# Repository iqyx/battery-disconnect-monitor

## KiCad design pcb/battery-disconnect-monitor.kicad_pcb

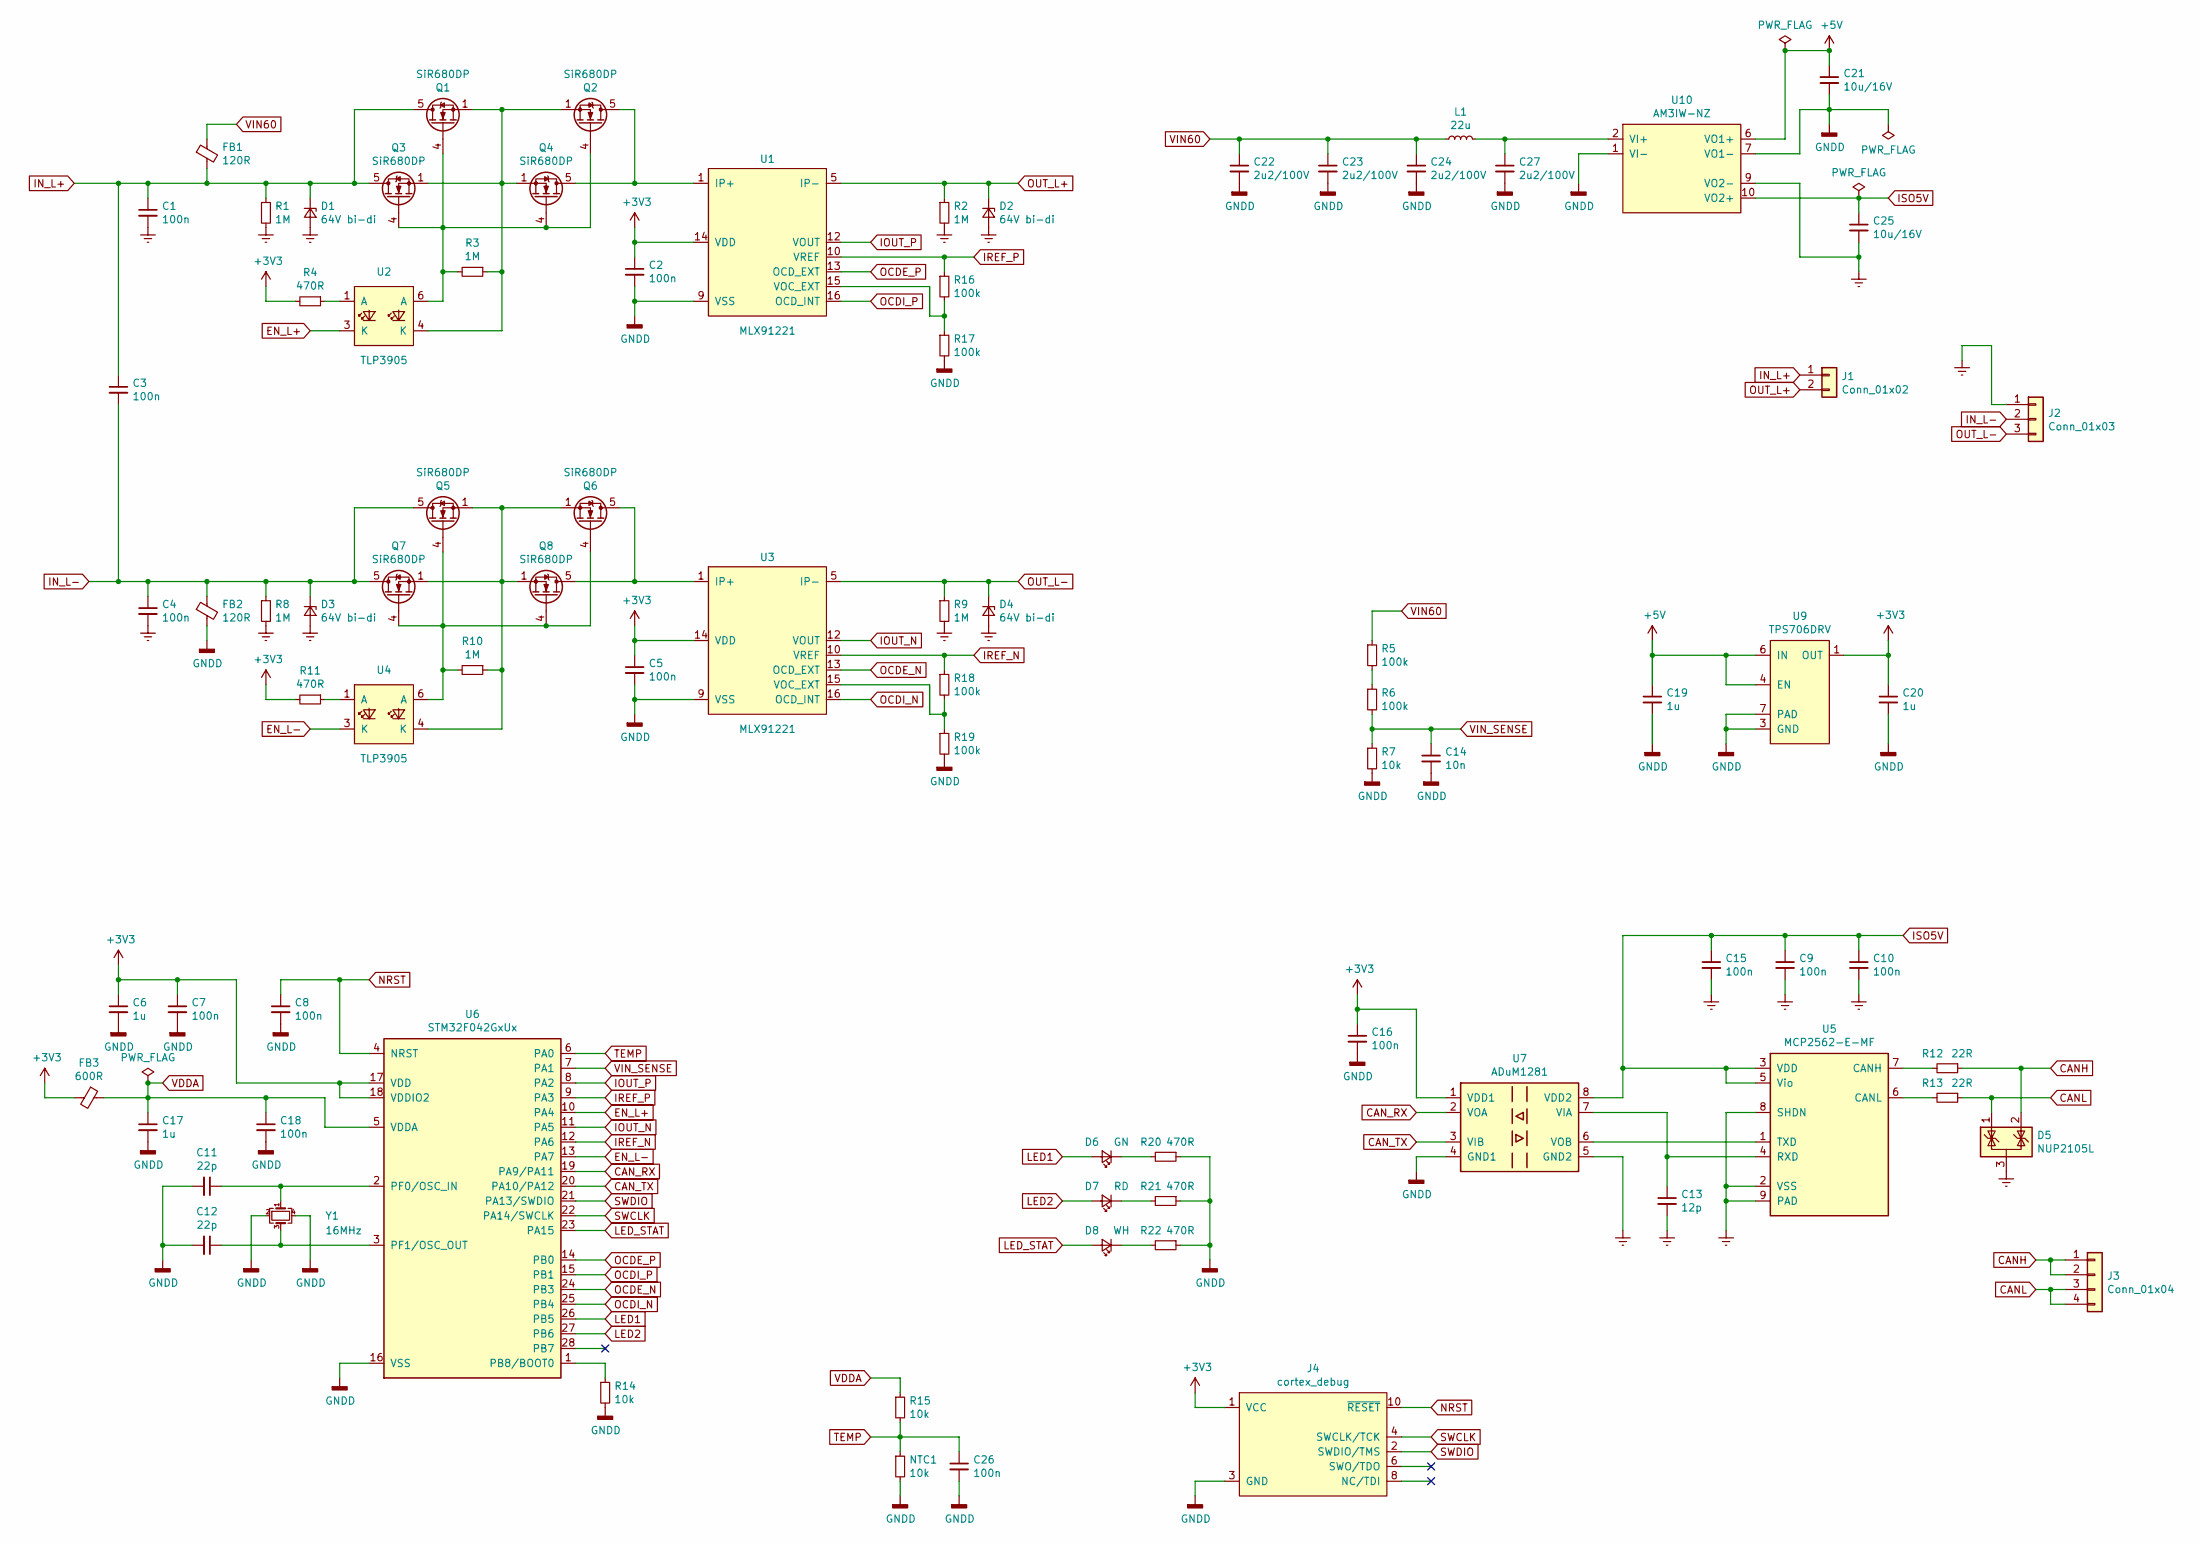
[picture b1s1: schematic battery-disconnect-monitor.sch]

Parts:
C1, C3, C4: 100n; C_1210_3225Metric
C2, C5, C7, C8, C9, C10, C15, C16, C18, C26: 100n; C_0603_1608Metric
C6, C17, C19, C20: 1u; C_0603_1608Metric
C11, C12: 22p; C_0603_1608Metric
C13: 12p; C_0603_1608Metric
C14: 10n; C_0603_1608Metric
C21, C25: 10u/16V; C_1206_3216Metric
C22, C23, C24, C27: 2u2/100V; C_1210_3225Metric
D1, D2, D3, D4: 64V bi-di; D_SMC
D5: NUP2105L; SOT-23
D6: GN; LED_0805_2012Metric
D7: RD; LED_0805_2012Metric
D8: WH; LED_0805_2012Metric
FB1, FB2: 120R; L_0805_2012Metric
FB3: 600R; L_0603_1608Metric
J1: Conn_01x02; DG270-10.0-02P
J2: Conn_01x03; DG270-10.0-03P
J3: Conn_01x04; PTSA-0.5-4-2.5-Z
J4: cortex_debug; CortexDebug_Vertical_SMD
L1: 22u; L_1210_3225Metric
NTC1: 10k; R_0603_1608Metric
Q1, Q2, Q3, Q4, Q5, Q6, Q7, Q8: SiR680DP; PowerPAK_SO-8_Single
R1, R2, R3, R8, R9, R10: 1M; R_1206_3216Metric
R4, R11, R20, R21, R22: 470R; R_0603_1608Metric
R5, R6: 100k; R_1206_3216Metric
R7: 10k; R_1206_3216Metric
R12, R13: 22R; R_0603_1608Metric
R14, R15: 10k; R_0603_1608Metric
R16, R17, R18, R19: 100k; R_0603_1608Metric
U1, U3: MLX91221; SOIC-16W_7.5x10.3mm_P1.27mm
U2, U4: TLP3905; SOIC-4_4.55x3.7mm_P2.54mm
U5: MCP2562-E-MF; DFN-8-1EP_3x3mm_P0.65mm_EP1.55x2.4mm
U6: STM32F042GxUx; QFN-28_4x4mm_P0.5mm
U7: ADuM1281; SOIC-8_3.9x4.9mm_P1.27mm
U9: TPS706DRV; DFN-6-1EP_2x2mm_P0.65mm_EP1x1.6mm
U10: AM3IW-NZ
Y1: 16MHz; Crystal_SMD_3225-4Pin_3.2x2.5mm

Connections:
+3V3: C2.1, C5.1, C6.1, C7.1, C16.1, C20.1, FB3.2, J4.1 (VCC), R4.2, R11.2, U1.14 (VDD), U3.14 (VDD), U6.17 (VDD), U6.18 (VDDIO2), U7.1 (VDD1), U9.1 (OUT)
+5V: C19.1, C21.1, U9.4 (EN), U9.6 (IN), U10.6 (VO1+)
CANH: D5.2 (K), J3.1, J3.2, R12.1
CANL: D5.1 (K), J3.3, J3.4, R13.1
CAN_RX: U6.19 (PA9/PA11), U7.2 (VOA)
CAN_TX: U6.20 (PA10/PA12), U7.3 (VIB)
EN_L+: U2.3 (K), U6.10 (PA4)
EN_L-: U4.3 (K), U6.13 (PA7)
Earth: C1.2, C4.2, C9.2, C10.2, C13.2, C15.2, C25.2, D1.2 (A), D2.2 (A), D3.2 (A), D4.2 (A), D5.3 (A), J2.1, R1.2, R2.2, R8.2, R9.2, U5.2 (VSS), U5.8 (SHDN), U5.9 (PAD), U7.5 (GND2), U10.9 (VO2-)
GNDD: C2.2, C5.2, C6.2, C7.2, C8.2, C11.2, C12.2, C14.2, C16.2, C17.2, C18.2, C19.2, C20.2, C21.2, C22.2, C23.2, C24.2, C26.2, C27.2, FB2.2, J4.3 (GND), J4.5 (GND), J4.9 (GND), NTC1.2, R7.2, R14.2, R17.2, R19.2, R20.1, R21.1, R22.1, U1.9 (VSS), U3.9 (VSS), U6.16 (VSS), U7.4 (GND1), U9.3 (GND), U9.7 (PAD), U10.1 (VI-), U10.7 (VO1-), Y1.2, Y1.4
IN_L+: C1.1, C3.1, D1.1 (K), FB1.2, J1.1, Q1.5 (D), Q3.5 (D), R1.1
IN_L-: C3.2, C4.1, D3.1 (K), FB2.1, J2.2, Q5.5 (D), Q7.5 (D), R8.1
IOUT_N: U3.12 (VOUT), U6.11 (PA5)
IOUT_P: U1.12 (VOUT), U6.8 (PA2)
IREF_N: R18.1, U3.10 (VREF), U6.12 (PA6)
IREF_P: R16.1, U1.10 (VREF), U6.9 (PA3)
ISO5V: C9.1, C10.1, C15.1, C25.1, U5.3 (VDD), U5.5 (Vio), U7.8 (VDD2), U10.10 (VO2+)
LED1: D6.2 (A), U6.26 (PB5)
LED2: D7.2 (A), U6.27 (PB6)
LED_STAT: D8.2 (A), U6.23 (PA15)
NRST: C8.1, J4.10 (~RESET~), U6.4 (NRST)
unnamed: C11.1, U6.2 (PF0/OSC_IN), Y1.1
unnamed: C12.1, U6.3 (PF1/OSC_OUT), Y1.3
unnamed: C13.1, U5.4 (RXD), U7.7 (VIA)
unnamed: C27.1, L1.2, U10.2 (VI+)
unnamed: D6.1 (K), R20.2
unnamed: D7.1 (K), R21.2
unnamed: D8.1 (K), R22.2
unnamed: Q1.1 (S), Q1.2 (S), Q1.3 (S), Q2.1 (S), Q2.2 (S), Q2.3 (S), Q3.1 (S), Q3.2 (S), Q3.3 (S), Q4.1 (S), Q4.2 (S), Q4.3 (S), R3.1, U2.4 (K)
unnamed: Q1.4 (G), Q2.4 (G), Q3.4 (G), Q4.4 (G), R3.2, U2.6 (A)
unnamed: Q2.5 (D), Q4.5 (D), U1.1 (IP+), U1.2 (IP+), U1.3 (IP+), U1.4 (IP+)
unnamed: Q5.1 (S), Q5.2 (S), Q5.3 (S), Q6.1 (S), Q6.2 (S), Q6.3 (S), Q7.1 (S), Q7.2 (S), Q7.3 (S), Q8.1 (S), Q8.2 (S), Q8.3 (S), R10.1, U4.4 (K)
unnamed: Q5.4 (G), Q6.4 (G), Q7.4 (G), Q8.4 (G), R10.2, U4.6 (A)
unnamed: Q6.5 (D), Q8.5 (D), U3.1 (IP+), U3.2 (IP+), U3.3 (IP+), U3.4 (IP+)
unnamed: R4.1, U2.1 (A)
unnamed: R5.2, R6.1
unnamed: R11.1, U4.1 (A)
unnamed: R12.2, U5.7 (CANH)
unnamed: R13.2, U5.6 (CANL)
unnamed: R14.1, U6.1 (PB8/BOOT0)
unnamed: R16.2, R17.1, U1.15 (VOC_EXT)
unnamed: R18.2, R19.1, U3.15 (VOC_EXT)
unnamed: U5.1 (TXD), U7.6 (VOB)
OCDE_N: U3.13 (OCD_EXT), U6.24 (PB3)
OCDE_P: U1.13 (OCD_EXT), U6.14 (PB0)
OCDI_N: U3.16 (OCD_INT), U6.25 (PB4)
OCDI_P: U1.16 (OCD_INT), U6.15 (PB1)
OUT_L+: D2.1 (K), J1.2, R2.1, U1.5 (IP-), U1.6 (IP-), U1.7 (IP-), U1.8 (IP-)
OUT_L-: D4.1 (K), J2.3, R9.1, U3.5 (IP-), U3.6 (IP-), U3.7 (IP-), U3.8 (IP-)
SWCLK: J4.4 (SWCLK/TCK), U6.22 (PA14/SWCLK)
SWDIO: J4.2 (SWDIO/TMS), U6.21 (PA13/SWDIO)
TEMP: C26.1, NTC1.1, R15.2, U6.6 (PA0)
VDDA: C17.1, C18.1, FB3.1, R15.1, U6.5 (VDDA)
VIN60: C22.1, C23.1, C24.1, FB1.1, L1.1, R5.1
VIN_SENSE: C14.1, R6.2, R7.1, U6.7 (PA1)

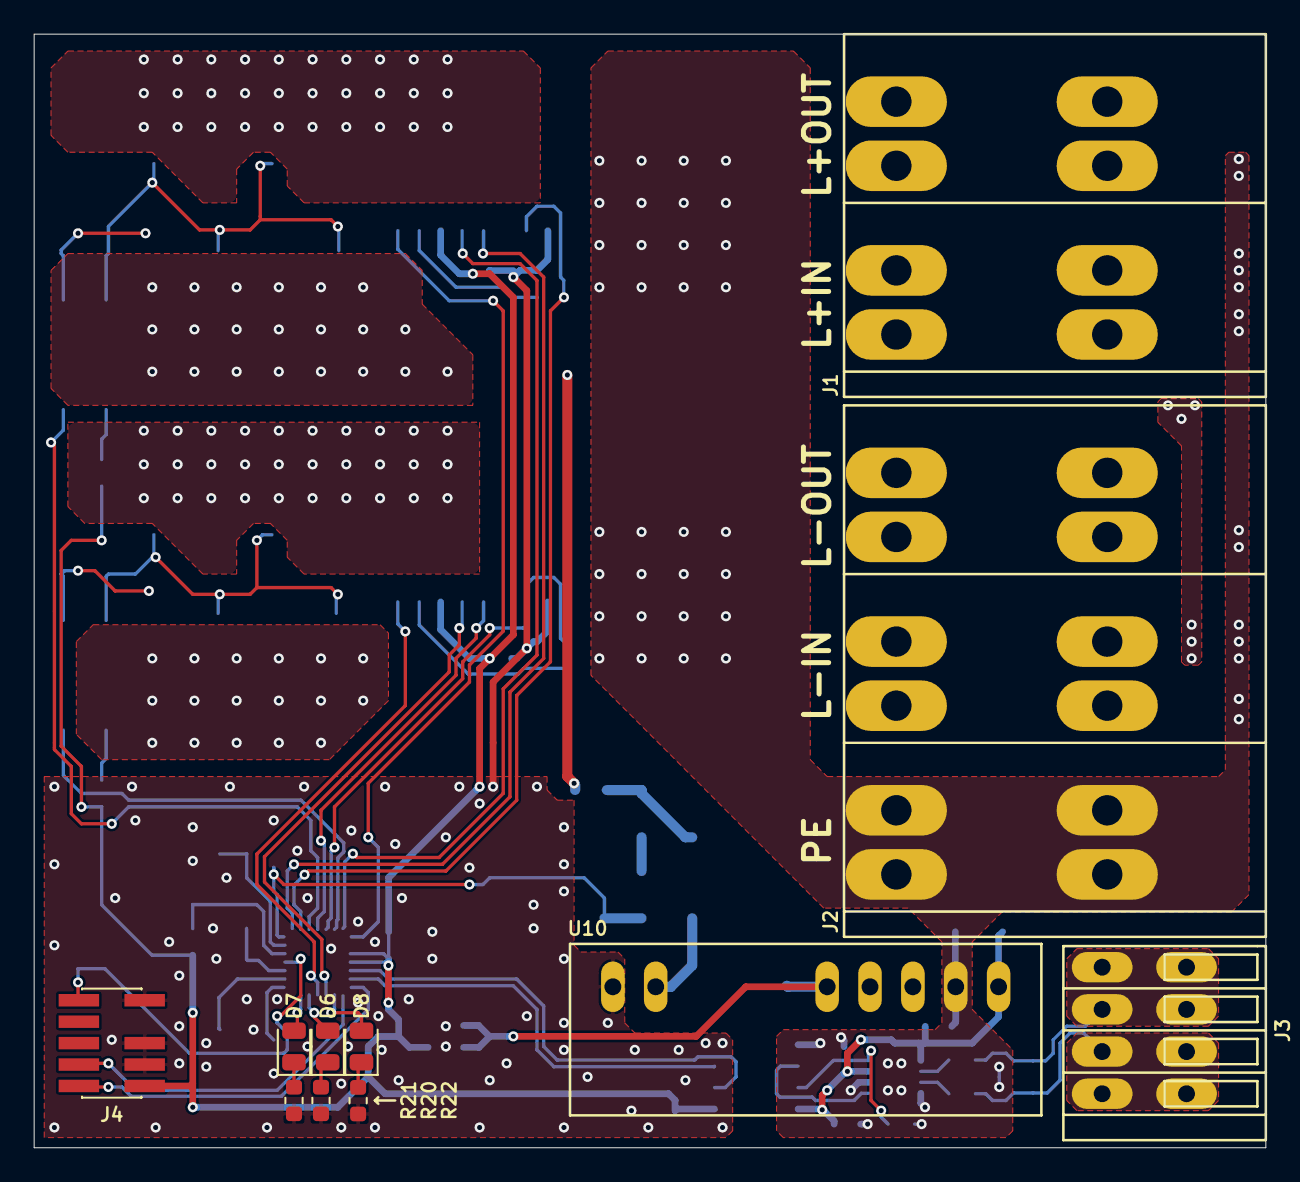
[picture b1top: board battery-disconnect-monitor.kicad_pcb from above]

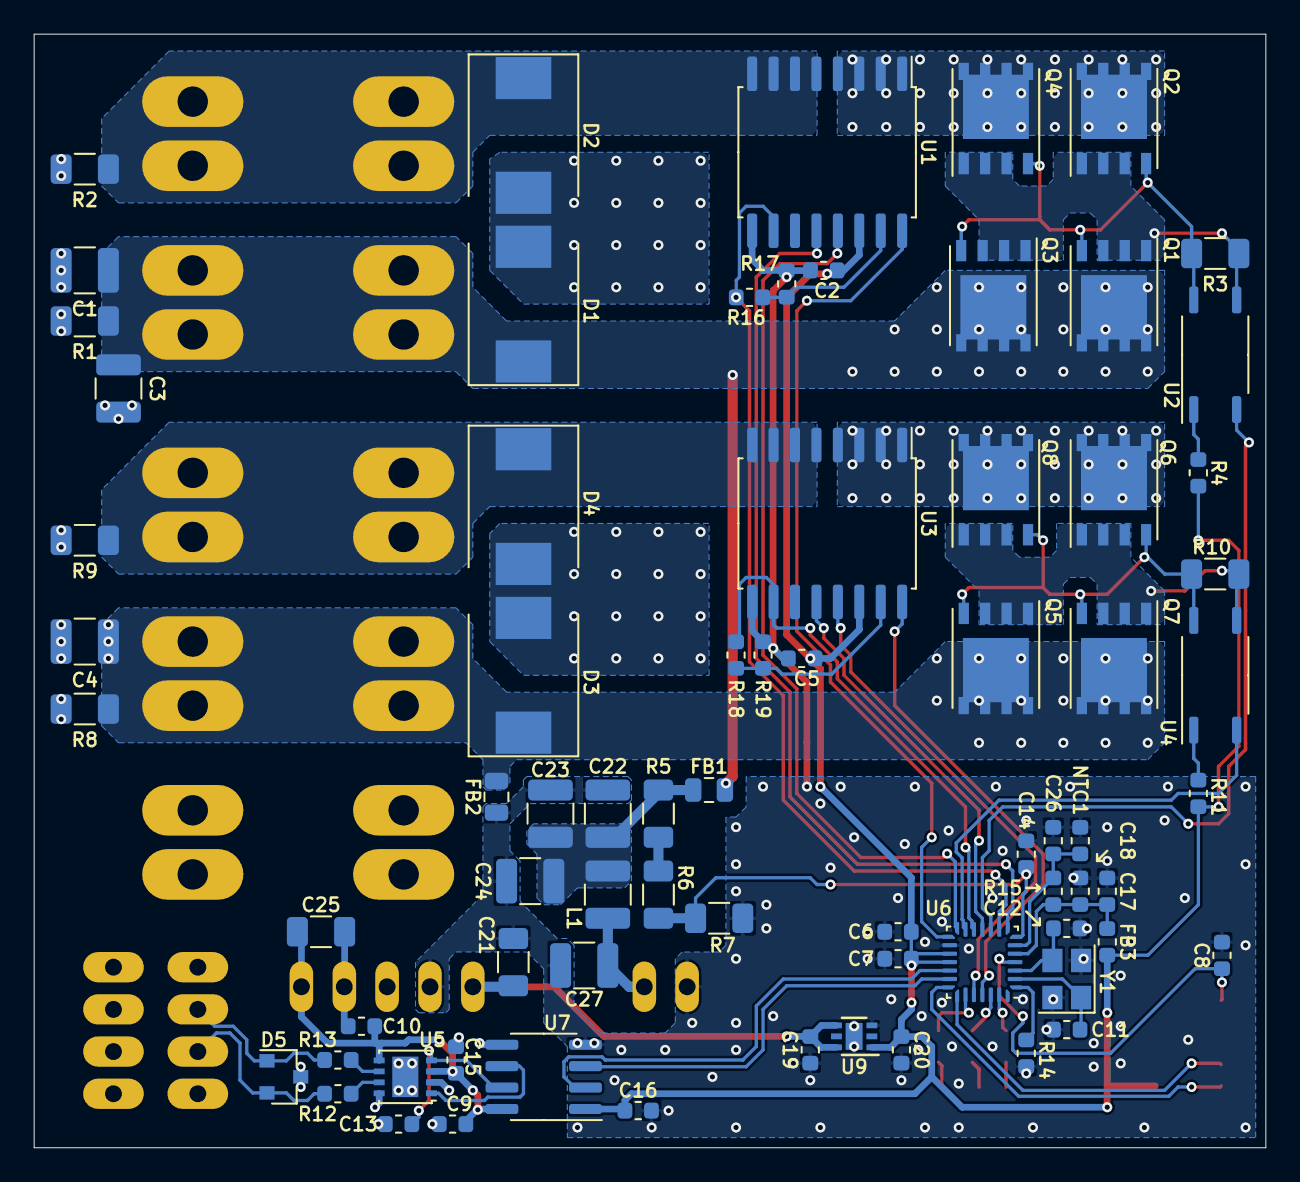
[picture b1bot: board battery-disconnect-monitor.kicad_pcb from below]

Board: 2 copper layers, 73.0 x 66.0 mm, 84 parts (73 on the bottom side), 55 nets.

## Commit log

2021-01-03 Add schematic and layout
2021-01-03 Add .gitignore to ignore temporary and backup files
